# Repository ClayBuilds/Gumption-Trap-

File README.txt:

GUMPTION TRAP

This project is open source, free for anyone to use for whatever you want. 
I coded/designed/built all this purely for hobby purposes and I'm happy to help others build onto it for their own projects.

Check out my youtube channel for a few videos explaining this stuff in action:
https://www.youtube.com/channel/UCnwIEK_l8J-6gFpHYlkmyig
or look up "Clay Builds" (@Clay-Builds) on youtube if that link doesn't work. 

My website is https://www.clay-p-mcpherson.com/ 
It might have some bonus pictures and stuff but it mostly just links to the youtube channel. 

Yee-Haw

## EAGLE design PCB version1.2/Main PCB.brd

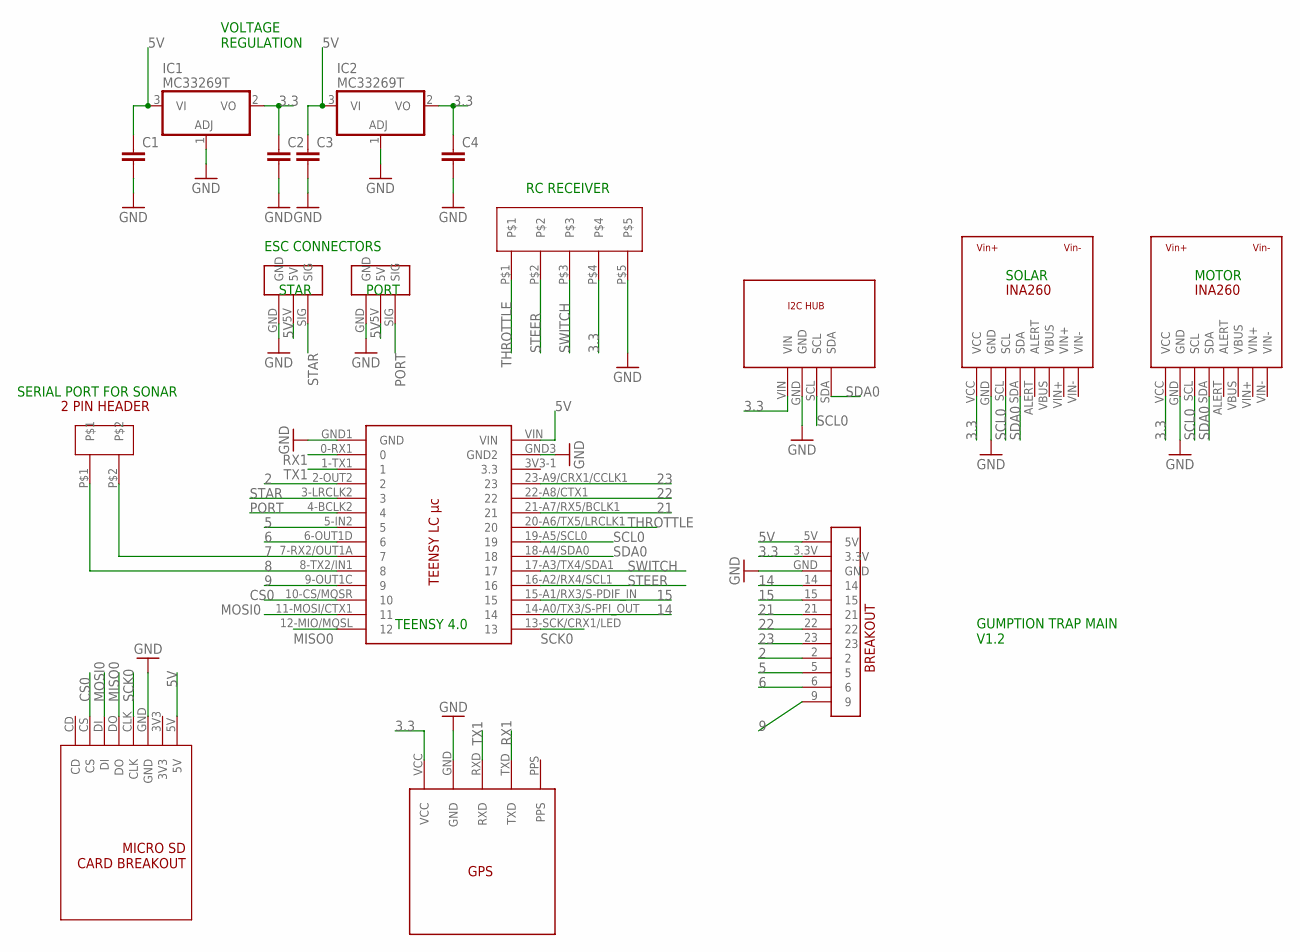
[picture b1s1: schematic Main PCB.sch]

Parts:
C1, C2, C3, C4: C2.5/2; C2.5-2
IC1, IC2: MC33269T; TO220V
MOTOR: INA260
PORT: SERVO3PIN
SOLAR: INA260
STAR: SERVO3PIN
U$1: TEENSYLC; TEENSY40
U$2: GPS
U$3: QT5HUB
U$4: SD2
U$5: 2PIN_JST-XH
U$6: 5PIN_JST-XH
U$8: BREAKOUT

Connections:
2: U$1.2-OUT2 (2), U$8.2
3.3: C2.1, C4.1, IC1.2 (VO), IC2.2 (VO), MOTOR.VCC, SOLAR.VCC, U$2.VCC, U$3.VIN, U$6.P$4, U$8.3.3V
5: U$1.5-IN2 (5), U$8.5
5V: C1.1, C3.1, IC1.3 (VI), IC2.3 (VI), PORT.5V, STAR.5V, U$1.VIN, U$4.5V, U$8.5V
6: U$1.6-OUT1D (6), U$8.6
7: U$1.7-RX2/OUT1A (7), U$5.P$2
8: U$1.8-TX2/IN1 (8), U$5.P$1
9: U$1.9-OUT1C (9), U$8.9
14: U$1.14-A0/TX3/S-PFI_OUT (14), U$8.14
15: U$1.15-A1/RX3/S-PDIF_IN (15), U$8.15
21: U$1.21-A7/RX5/BCLK1 (21), U$8.21
22: U$1.22-A8/CTX1 (22), U$8.22
23: U$1.23-A9/CRX1/CCLK1 (23), U$8.23
CS0: U$1.10-CS/MQSR (10), U$4.CS
GND: C1.2, C2.2, C3.2, C4.2, IC1.1 (ADJ), IC2.1 (ADJ), MOTOR.GND, PORT.GND, SOLAR.GND, STAR.GND, U$1.GND1 (GND), U$1.GND3 (GND2), U$2.GND, U$3.GND, U$4.GND, U$6.P$5, U$8.GND
MISO0: U$1.12-MIO/MQSL (12), U$4.DO
MOSI0: U$1.11-MOSI/CTX1 (11), U$4.DI
PORT: PORT.SIG, U$1.4-BCLK2 (4)
RX1: U$1.0-RX1 (0), U$2.TXD
SCK0: U$1.13-SCK/CRX1/LED (13), U$4.CLK
SCL0: MOTOR.SCL, SOLAR.SCL, U$1.19-A5/SCL0 (19), U$3.SCL
SDA0: MOTOR.SDA, SOLAR.SDA, U$1.18-A4/SDA0 (18), U$3.SDA
STAR: STAR.SIG, U$1.3-LRCLK2 (3)
STEER: U$1.16-A2/RX4/SCL1 (16), U$6.P$2
SWITCH: U$1.17-A3/TX4/SDA1 (17), U$6.P$3
THROTTLE: U$1.20-A6/TX5/LRCLK1 (20), U$6.P$1
TX1: U$1.1-TX1 (1), U$2.RXD

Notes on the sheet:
SOLAR
MOTOR
STAR
PORT
GUMPTION TRAP MAIN V1.2
TEENSY 4.0
RC RECEIVER
ESC CONNECTORS
VOLTAGE REGULATION
SERIAL PORT FOR SONAR

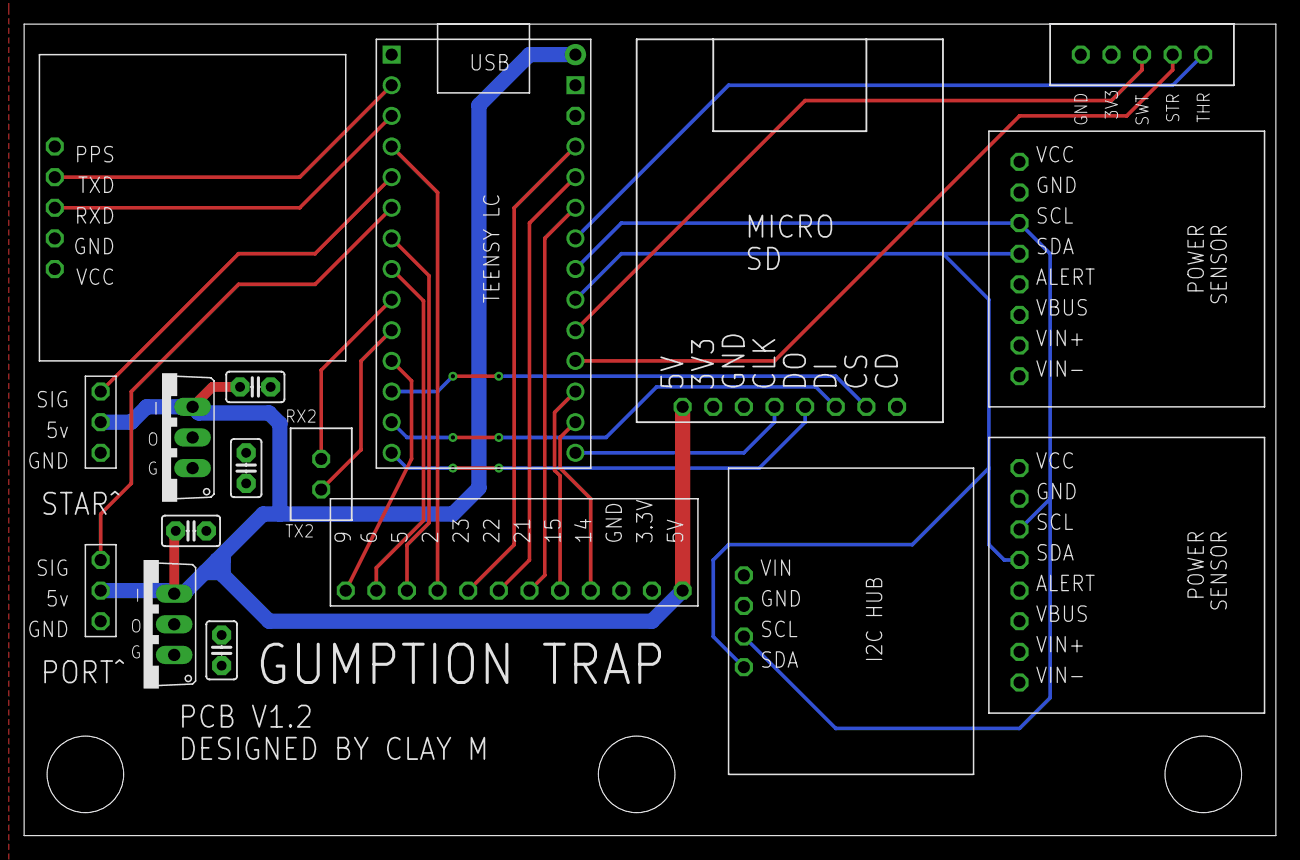
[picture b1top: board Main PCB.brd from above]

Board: 2 copper layers, 103.8 x 67.3 mm, 17 parts (0 on the bottom side), 27 nets.

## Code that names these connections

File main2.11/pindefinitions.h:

//This file includes all necessary pin definitions as wired on pcb 
//note: LED_BUILTIN can't be used cause pin 13 is SCK

#ifndef PIN_DEFINITIONS_h
#define PIN_DEFINITIONS_h

const byte gpsrx = 1;   //don't think I actually need rx/tx since I'm not using software serial anymore. These are the serial pins for the GPS module
const byte gpstx = 0;
const byte smot = 3;    //starboard motor PWM signal to ESC
const byte pmot = 4;    //port motor PWM signal to ESC
const byte throt = 20;  //Throttle PWM signal coming from radio receiver in manual mode
const byte steer = 16;  //Steering PWM signal coming from radio receiver in manual mode
const byte swt = 17;    //auxiliary switch signal coming from radio receiver. toggles between auto/manual modes.
const byte cs = 10;     //chip select for SD card
const byte mosi = 11;   // other SPI pins 
const byte miso = 12;
const byte sck = 13;
const byte ping_arduinorx = 7; //don't think I actually need rx/tx since I'm not using software serial anymore. These are serial pins for the sonar module. 
const byte ping_arduinotx = 8;

#endif

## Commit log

2023-03-07 Add files via upload
    COORDS.TXT is an example of coordinates readable by the main code. Number in first line is the total number of included coordinate pairs. Change these values to any latitude/longitude.
2023-03-07 Add files via upload
    Matlab files are a little rough but these are what I used to create the depth plots I showed in the video.
2023-03-07 Add files via upload
    PCB files should include everything you need to re-create this PCB.
